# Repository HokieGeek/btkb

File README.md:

# btkb

I have a fantastic Pok3r mech that, annoyingly, uses a cable to connect to my computer. I am building a module that includes a decent battery and bluetooth modem to replace the cable.

## Prototype

# Schematics
## Power module

## Bluetooth module

# Board
## Power module

## Bluetooth Module

# Parts list
[Mouser project](https://www.mouser.com/ProjectManager/ProjectDetail.aspx?ProjectGUID=d7660f5c-4cd6-4143-9f81-287e7d12060d)

## ICs
- [RN-42 HID](http://www.sparkfun.com/datasheets/Wireless/Bluetooth/rn-42-ds.pdf) - Bluetooth modem with HID firmware
- [BSS138](https://www.fairchildsemi.com/datasheets/BS/BSS138.pdf) - MOSFET N-Channel Logic
- [MCP73831T](https://www.sparkfun.com/datasheets/Prototyping/Batteries/MCP73831T.pdf) - Li-Ion battery 4.5V voltage regulator
- [LM25775](http://www.ti.com/lit/ds/symlink/uc2577-adj.pdf) - Adjustable step-up voltage regulator

## Other components

* LEDs
 * 1x Red (data in to BT)
 * 1x Green (data out of BT)
 * Some sort of LED for battery status (TODO)
* Resistors
 * 7x 10 kΩ
 * 1x 2 kΩ
 * 3x 330 Ω
* Capacitors
 * 2x 10 µF (polarized)
 * 2x 4.7 µF
 * 2x 1 µF

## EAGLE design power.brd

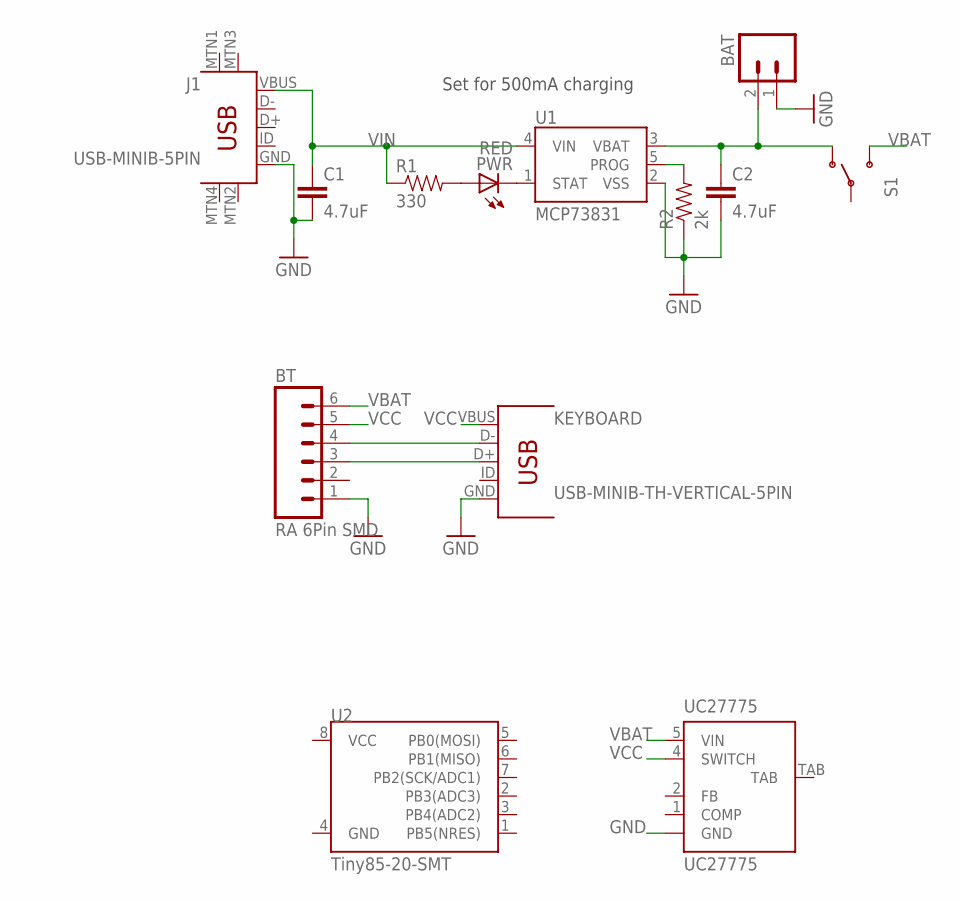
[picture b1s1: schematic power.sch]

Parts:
BAT: LiPo Battery; JST-2-SMD
BT: RA 6Pin SMD; 1X06-SMD-NOHOLES
C1, C2: 4.7uF; 0805-CAP
J1: USB-MINIB-5PIN; USB-MINIB
KEYBOARD: USB-MINIB-TH-VERTICAL-5PIN; USB-MINIB-TH-VERTICAL
PWR: RED; LED-0603
R1: 330; 0805
R2: 2k; 0805
S1: SWITCH-SPDT-SMD-A; SWITCH-SPST-SMD-A
U1: MCP73831; SOT23-5
U2: Tiny85-20-SMT; SO08-EIAJ
UC27775: UC27775; TO263_5

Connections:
GND: BAT.1, BT.1, C1.2, C2.2, J1.GND, KEYBOARD.GND, R2.1, U1.2 (VSS), UC27775.3 (GND)
unnamed: BT.4, KEYBOARD.D-
unnamed: BT.3, KEYBOARD.D+
unnamed: PWR.A, R1.2
PROG: R2.2, U1.5 (PROG)
STAT: PWR.C, U1.1 (STAT)
VBAT: BT.6, S1.3 (S), UC27775.5 (VIN)
VBAT2: BAT.2, C2.1, S1.1 (O), U1.3 (VBAT)
VCC: BT.5, KEYBOARD.VBUS, UC27775.4 (SWITCH)
VIN: C1.1, J1.VBUS, R1.1, U1.4 (VIN)

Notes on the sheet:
Set for 500mA charging

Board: 2 copper layers, 13 parts (8 on the bottom side), 10 nets, no tracks yet.

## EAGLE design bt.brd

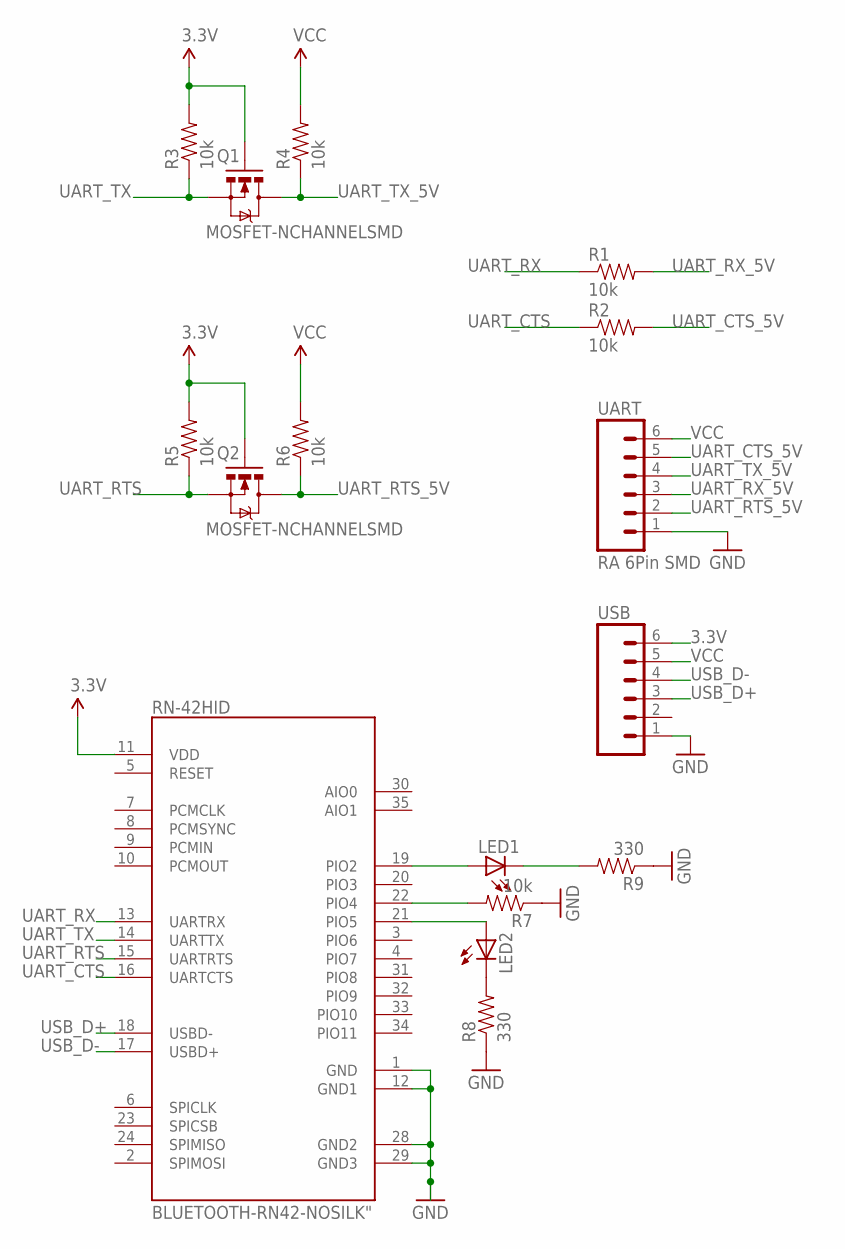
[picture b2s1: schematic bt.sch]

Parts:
LED1, LED2: LEDCHIP-LED0805; CHIP-LED0805
Q1, Q2: MOSFET-NCHANNELSMD; SOT23-3
R1, R2, R3, R4, R5, R6, R7: 10k; 0805
R8, R9: 330; 0805
RN-42HID: BLUETOOTH-RN42-NOSILK"; RN41
UART: RA 6Pin SMD; 1X06-SMD-NOHOLES
USB: M06SMD-FEMALE-V2-NOSILK; 1X06-SMD-FEMALE-V2-NOSILK

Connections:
3.3V: Q1.1 (G), Q2.1 (G), R3.2, R5.2, USB.6
GND: R7.1, R8.1, R9.1, RN-42HID.1 (GND), RN-42HID.12 (GND1), RN-42HID.28 (GND2), RN-42HID.29 (GND3), UART.1, USB.1
unnamed: LED2.C, R8.2
unnamed: LED1.C, R9.2
unnamed: LED1.A, RN-42HID.19 (PIO2)
unnamed: R7.2, RN-42HID.22 (PIO4)
unnamed: LED2.A, RN-42HID.21 (PIO5)
UART_CTS: R2.1, RN-42HID.16 (UARTCTS)
UART_CTS_5V: R2.2, UART.5
UART_RTS: Q2.2 (S), R5.1, RN-42HID.15 (UARTRTS)
UART_RTS_5V: Q2.3 (D), R6.1, UART.2
UART_RX: R1.1, RN-42HID.13 (UARTRX)
UART_RX_5V: R1.2, UART.3
UART_TX: Q1.2 (S), R3.1, RN-42HID.14 (UARTTX)
UART_TX_5V: Q1.3 (D), R4.1, UART.4
USB_D+: RN-42HID.18 (USBD-), USB.3
USB_D-: RN-42HID.17 (USBD+), USB.4
VCC: R4.2, R6.2, RN-42HID.11 (VDD), UART.6, USB.5

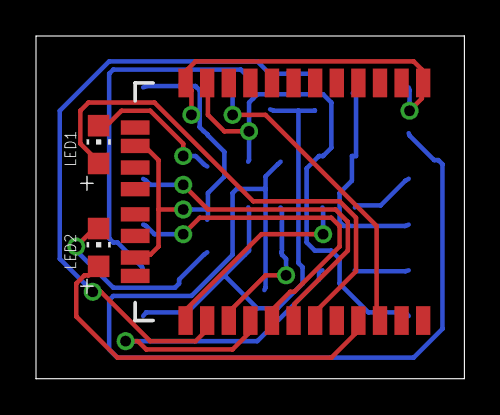
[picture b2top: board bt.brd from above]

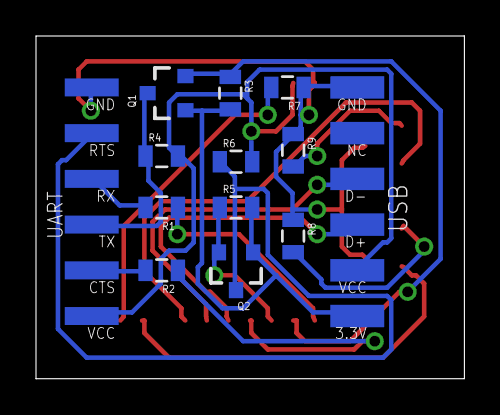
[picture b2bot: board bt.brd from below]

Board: 2 copper layers, 23.8 x 19.0 mm, 16 parts (13 on the bottom side), 18 nets.

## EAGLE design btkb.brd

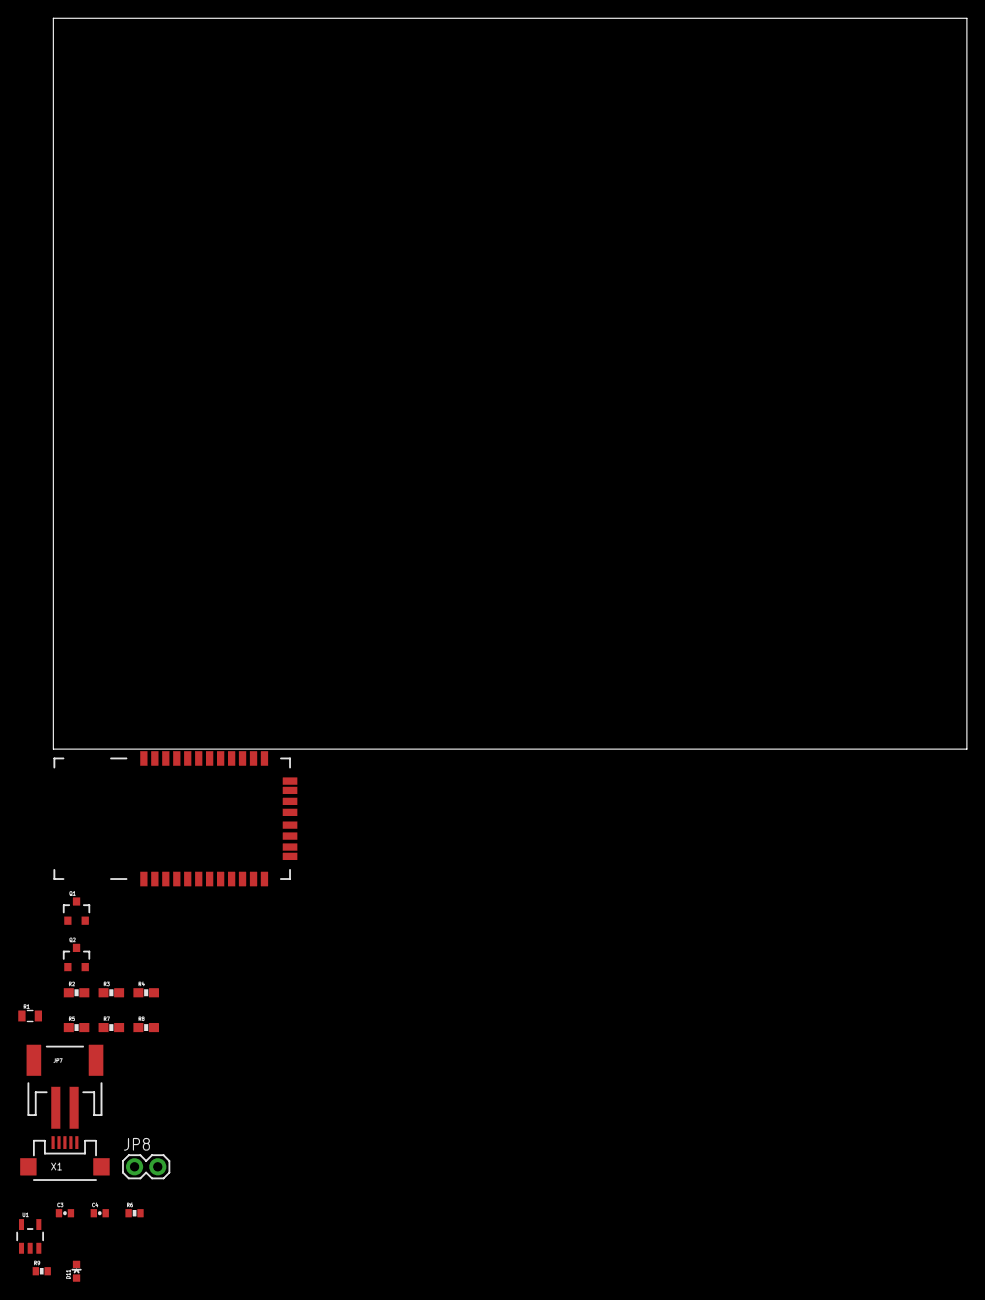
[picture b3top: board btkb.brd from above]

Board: 2 copper layers, 100.0 x 80.0 mm, 19 parts (0 on the bottom side), 11 nets, no tracks yet.

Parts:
C3, C4: 4.7uF; 0402-CAP
D11: RED; LED-0603
IC1: BLUETOOTH-RN42 HID; RN41
JP7: LiPo Battery; JST-2-SMD
JP8: 1X02
Q1, Q2: MOSFET-NCHANNELSMD; SOT23-3
R1: 10k; 0805
R2, R3, R4, R5, R7, R8: 10K; 0603-RES
R6: 330; 0402-RES
R9: 2K; 0402-RES
U1: MCP73831; SOT23-5
X1: Micro USB; USB-MICROB

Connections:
3.3V: Q1.1, Q2.1, R3.1, R7.1
GND: C3.2, C4.2, IC1.1, IC1.12, IC1.28, IC1.29, JP7.1, JP8.1, R9.2, U1.2, X1.GND
unnamed: D11.A, R6.1
PROG: R9.1, U1.5
RTS: Q2.2, R7.2
RTS_5V: Q2.3, R8.2
STAT: D11.C, U1.1
TX: Q1.2, R3.2
TX_5V: Q1.3, R4.2
VCC: C4.1, JP7.2, JP8.2, R4.1, R8.1, U1.3
VIN: C3.1, R6.2, U1.4, X1.VBUS

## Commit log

2015-10-13 Ignoring the usuals for this
2015-10-13 Adding the placeholder files
2015-10-14 I added the RN-42 to the schematic! lol!
2015-10-14 EAGLE!
2015-10-19 Starting to flesh this out.
2015-10-19 Fleshing out some more
2015-10-23 Adding datasheets
2015-10-23 Added datasheets and discrete components
2015-10-26 No battery gauge and fixing rn42 datasheet
2015-10-26 Added components copy pasta'ed from other schematics
2015-10-26 Organizing stuffs
2015-10-26 Updated component list
    Still doesn't include the boost circuit
2015-10-28 Starting to flesh this out
2015-10-28 Fixed the TPS being used
2015-10-28 Updating with changes
2015-10-29 More updates
2015-10-29 I don't think I will be using the TPS this go-around
2015-10-30 Tried to route the BT board.... Do I need 4 layers for this?
2015-10-30 Updated headers to remove annoying holes and now using my own library
2015-10-30 Updated height of board to match bt board and rearranged components
2015-10-30 Removed silk from bt module and renamed headers
2015-10-30 Flipped the board around
2015-10-30 Putting more info on this thing to help me out
2015-10-30 Changing which pins are the USB data pins to match the standard
2015-10-30 Adding a spot for the protoype pics that are forthcoming
2015-10-30 Adding the pictures that already exist, albeit somewhat dated
2015-10-31 Updated and created images
2015-11-02 Got a good handle on the bt module so went ahead and ordered one
2015-11-02 Added prototype pic
2015-11-02 Added a switch and cleaned up the drawings
2015-11-02 Added a switch and playing around with the arrangement
2015-11-04 Using mini usb instead of micro
2015-11-04 Eagle project

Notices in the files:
parts and their libraries:
SparkFun-Resistors: Licensing: Creative Commons ShareAlike 4.0 International - https://creativecommons.org/licenses/by-sa/4.0
